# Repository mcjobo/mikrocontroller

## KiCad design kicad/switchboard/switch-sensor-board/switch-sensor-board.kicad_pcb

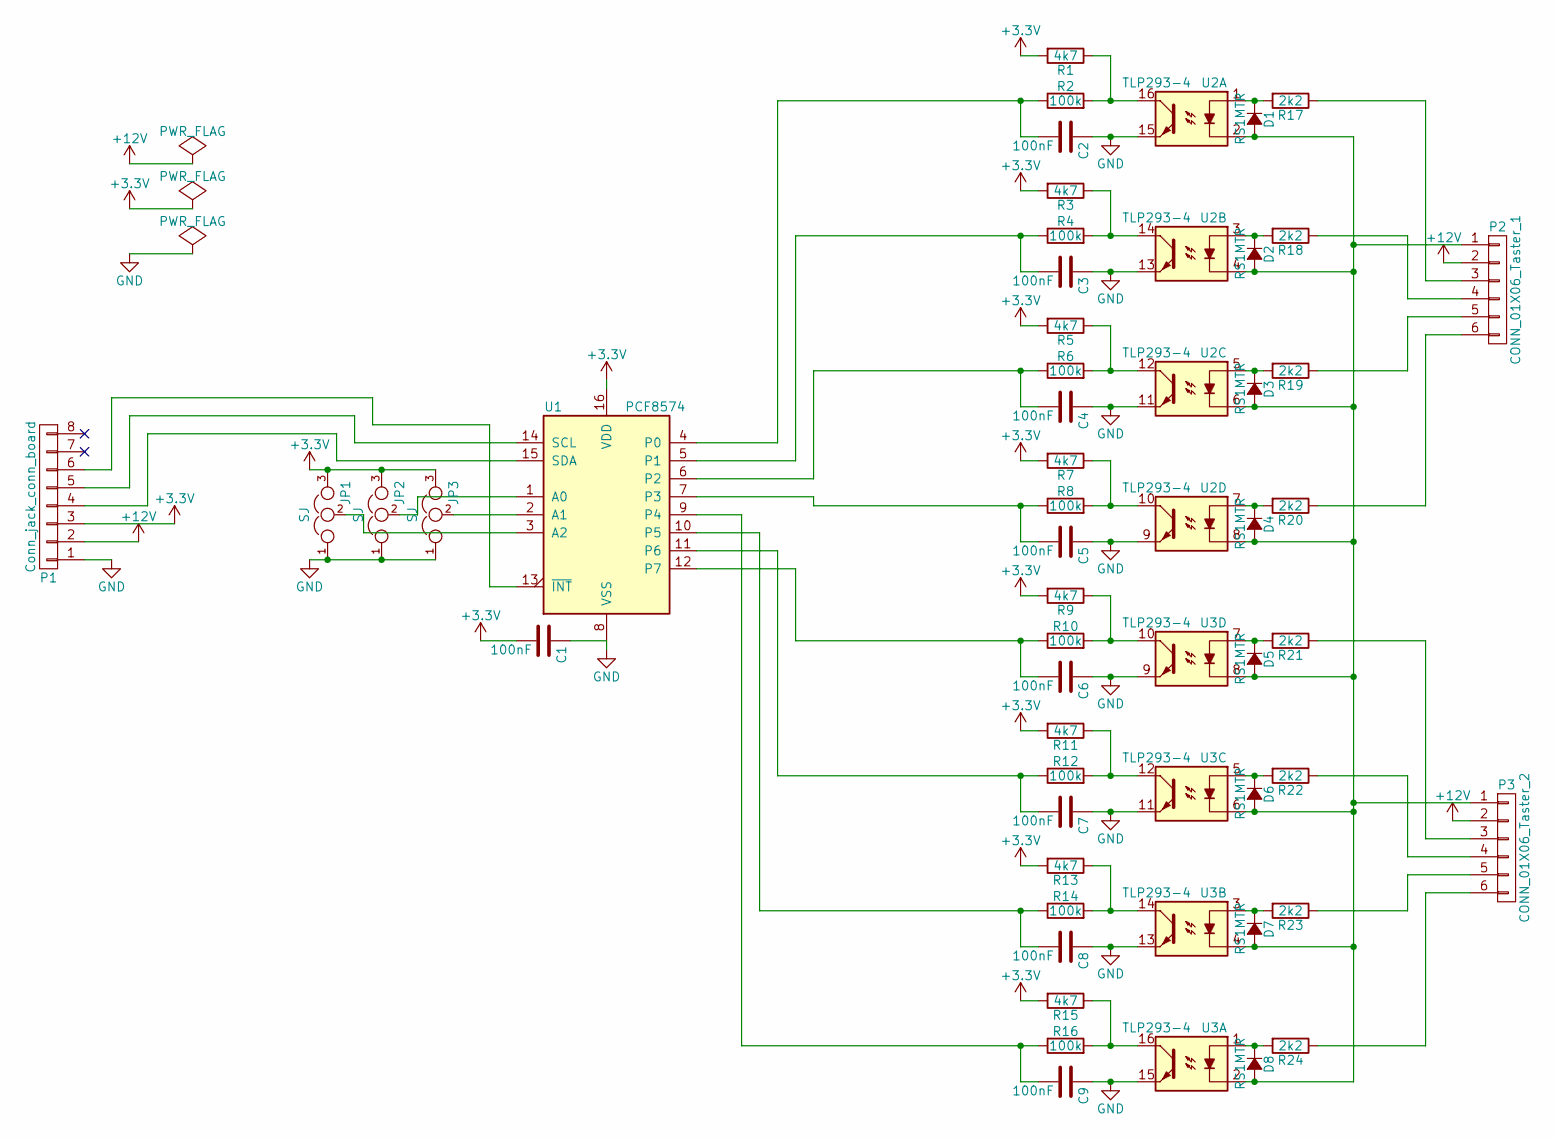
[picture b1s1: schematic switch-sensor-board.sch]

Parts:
C1, C2, C3, C4, C5, C6, C7, C8, C9: 100nF; C_1206_HandSoldering; Digi-Key 1276-2854-1-ND
D1, D2, D3, D4, D5, D6, D7, D8: RS1MTR; SMA_Handsoldering; Digi-Key 1655-1501-1-ND
JP1, JP2, JP3: SJ; solder-jumper-3er
P1: Conn_jack_conn_board; 4x2pin_50mil_header; Digi-Key S9007E-04-ND
P2: CONN_01X06_Taster_1; bornier6; Digi-Key ED2229-ND
P3: CONN_01X06_Taster_2; bornier6; Digi-Key ED2229-ND
R1, R3, R5, R7, R9, R11, R13, R15: 4k7; R_1206_HandSoldering; Digi-Key RHM4.7YCT-ND
R2, R4, R6, R8, R10, R12, R14, R16: 100k; R_1206_HandSoldering; Digi-Key RHM100KYCT-ND
R17, R18, R19, R20, R21, R22, R23, R24: 2k2; R_1206_HandSoldering; Digi-Key RHM2.2KYCT-ND
U1: PCF8574; SO-16-W; Digi-Key 568-1076-5-ND
U2, U3: TLP293-4; SO-16-N; Digi-Key TLP293-4(LGBE-ND

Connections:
+3V3: C1.2, JP1.3, JP2.3, JP3.3, P1.3, R1.2, R3.2, R5.2, R7.2, R9.2, R11.2, R13.2, R15.2, U1.16 (VDD)
+12V: P1.2, P2.2, P3.2
GND: C1.1, C2.1, C3.1, C4.1, C5.1, C6.1, C7.1, C8.1, C9.1, JP1.1, JP2.1, JP3.1, P1.1, U1.8 (VSS), U2.9, U2.11, U2.13, U2.15, U3.9, U3.11, U3.13, U3.15
unnamed: C2.2, R2.1, U1.4 (P0)
unnamed: C3.2, R4.1, U1.5 (P1)
unnamed: C4.2, R6.1, U1.6 (P2)
unnamed: C5.2, R8.1, U1.7 (P3)
unnamed: C6.2, R10.1, U1.12 (P7)
unnamed: C7.2, R12.1, U1.11 (P6)
unnamed: C8.2, R14.1, U1.10 (P5)
unnamed: C9.2, R16.1, U1.9 (P4)
unnamed: D1.1 (K), R17.2, U2.1
unnamed: D1.2 (A), D2.2 (A), D3.2 (A), D4.2 (A), D5.2 (A), D6.2 (A), D7.2 (A), D8.2 (A), P2.1, P3.1, U2.2, U2.4, U2.6, U2.8, U3.2, U3.4, U3.6, U3.8
unnamed: D2.1 (K), R18.2, U2.3
unnamed: D3.1 (K), R19.2, U2.5
unnamed: D4.1 (K), R20.2, U2.7
unnamed: D5.1 (K), R21.2, U3.7
unnamed: D6.1 (K), R22.2, U3.5
unnamed: D7.1 (K), R23.2, U3.3
unnamed: D8.1 (K), R24.2, U3.1
unnamed: JP1.2, U1.3 (A2)
unnamed: JP2.2, U1.1 (A0)
unnamed: JP3.2, U1.2 (A1)
unnamed: P1.4, U1.15 (SDA)
unnamed: P1.5, U1.14 (SCL)
unnamed: P1.6, U1.13 (~INT~)
unnamed: P2.3, R17.1
unnamed: P2.4, R18.1
unnamed: P2.5, R19.1
unnamed: P2.6, R20.1
unnamed: P3.3, R21.1
unnamed: P3.4, R22.1
unnamed: P3.5, R23.1
unnamed: P3.6, R24.1
unnamed: R1.1, R2.2, U2.16
unnamed: R3.1, R4.2, U2.14
unnamed: R5.1, R6.2, U2.12
unnamed: R7.1, R8.2, U2.10
unnamed: R9.1, R10.2, U3.10
unnamed: R11.1, R12.2, U3.12
unnamed: R13.1, R14.2, U3.14
unnamed: R15.1, R16.2, U3.16

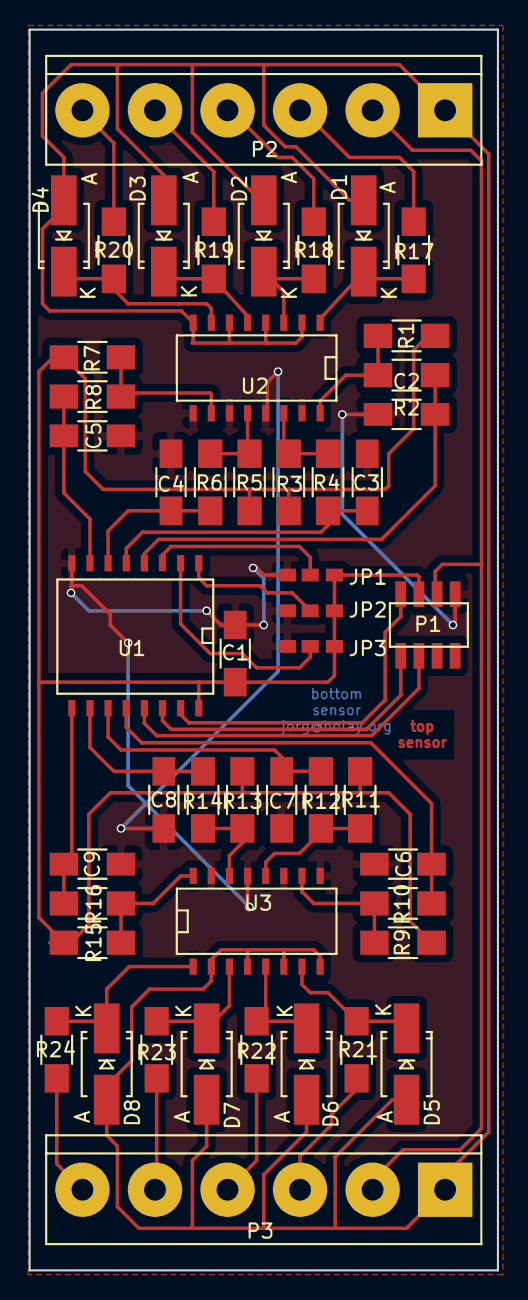
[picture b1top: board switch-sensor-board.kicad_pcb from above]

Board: 2 copper layers, 32.8 x 86.9 mm, 50 parts (0 on the bottom side), 42 nets.

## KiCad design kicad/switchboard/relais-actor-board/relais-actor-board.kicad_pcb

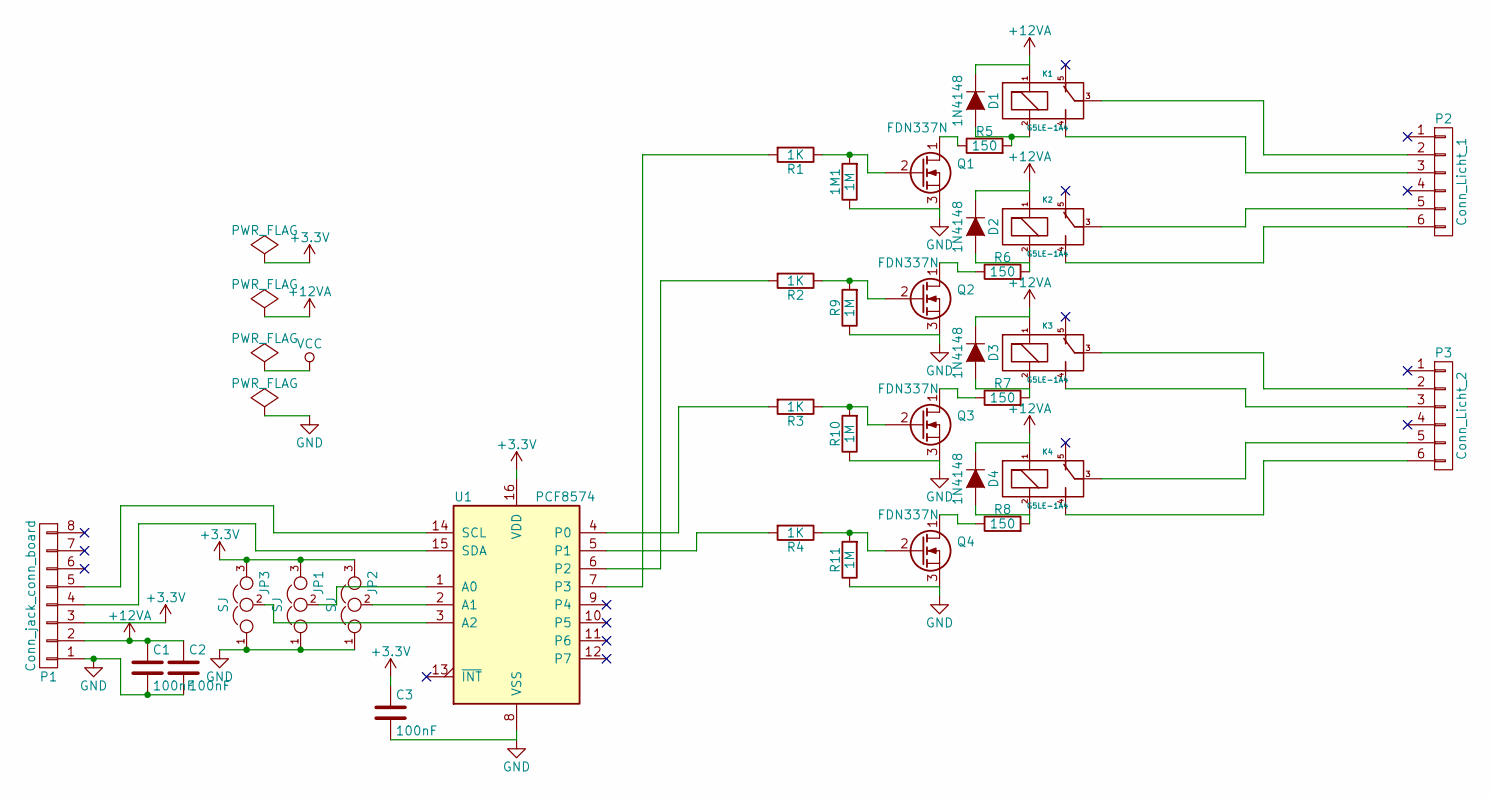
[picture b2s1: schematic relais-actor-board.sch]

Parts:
1M1: 1M; R_1206_HandSoldering; Digi-Key 311-1.0MERCT-ND
C1, C2, C3: 100nF; C_1206_HandSoldering; Digi-Key 1276-2854-1-ND
D1, D2, D3, D4: 1N4148; SOD-123; Digi-Key 1N4148W-FDICT-ND
JP1, JP2, JP3: SJ; solder-jumper-3er
K1, K2, K3, K4: G5LE-1A4; Relais-12V-Schlieser; Digi-Key PB876-ND
P1: Conn_jack_conn_board; 4x2pin_50mil_header; Digi-Key S9007E-04-ND
P2: Conn_Licht_1; bornier6; Digi-Key ED2229-ND
P3: Conn_Licht_2; bornier6; Digi-Key ED2229-ND
Q1, Q2, Q3, Q4: FDN337N; SOT-23_Handsoldering-FDN-337N; Digi-Key FDN337NTR-ND
R1, R2, R3, R4: 1K; R_1206_HandSoldering; Digi-Key 311-1.0KERCT-ND
R5, R6, R7, R8: 150; R_1206_HandSoldering; Digi-Key RHM150YCT-ND
R9, R10, R11: 1M; R_1206_HandSoldering; Digi-Key 311-1.0MERCT-ND
U1: PCF8574; SO-16-W; Digi-Key 568-1076-5-ND

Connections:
+3V3: C3.1, JP1.3, JP2.3, JP3.3, P1.3, U1.16 (VDD)
+12VA: C1.1, C2.1, D1.1 (K), D2.1 (K), D3.1 (K), D4.1 (K), K1.1, K2.1, K3.1, K4.1, P1.2
GND: 1M1.1, C1.2, C2.2, C3.2, JP1.1, JP2.1, JP3.1, P1.1, Q1.3 (S), Q2.3 (S), Q3.3 (S), Q4.3 (S), R9.1, R10.1, R11.1, U1.8 (VSS)
unnamed: 1M1.2, Q1.2 (G), R1.1
unnamed: D1.2 (A), K1.2, R5.2
unnamed: D2.2 (A), K2.2, R6.2
unnamed: D3.2 (A), K3.2, R7.2
unnamed: D4.2 (A), K4.2, R8.2
unnamed: JP1.2, U1.1 (A0)
unnamed: JP2.2, U1.2 (A1)
unnamed: JP3.2, U1.3 (A2)
unnamed: K1.3, P2.2
unnamed: K1.4, P2.3
unnamed: K2.3, P2.5
unnamed: K2.4, P2.6
unnamed: K3.3, P3.2
unnamed: K3.4, P3.3
unnamed: K4.3, P3.5
unnamed: K4.4, P3.6
unnamed: P1.4, U1.15 (SDA)
unnamed: P1.5, U1.14 (SCL)
unnamed: Q1.1 (D), R5.1
unnamed: Q2.1 (D), R6.1
unnamed: Q2.2 (G), R2.1, R9.2
unnamed: Q3.1 (D), R7.1
unnamed: Q3.2 (G), R3.1, R10.2
unnamed: Q4.1 (D), R8.1
unnamed: Q4.2 (G), R4.1, R11.2
unnamed: R1.2, U1.7 (P3)
unnamed: R2.2, U1.6 (P2)
unnamed: R3.2, U1.4 (P0)
unnamed: R4.2, U1.5 (P1)

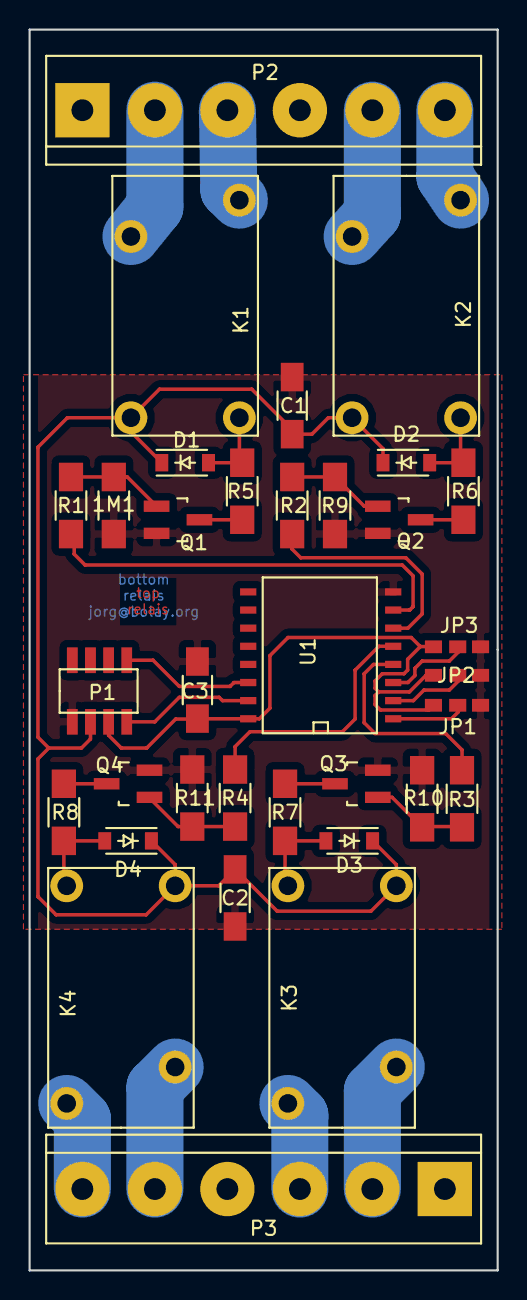
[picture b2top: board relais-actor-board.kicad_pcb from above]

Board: 2 copper layers, 32.8 x 86.9 mm, 34 parts (0 on the bottom side), 32 nets.

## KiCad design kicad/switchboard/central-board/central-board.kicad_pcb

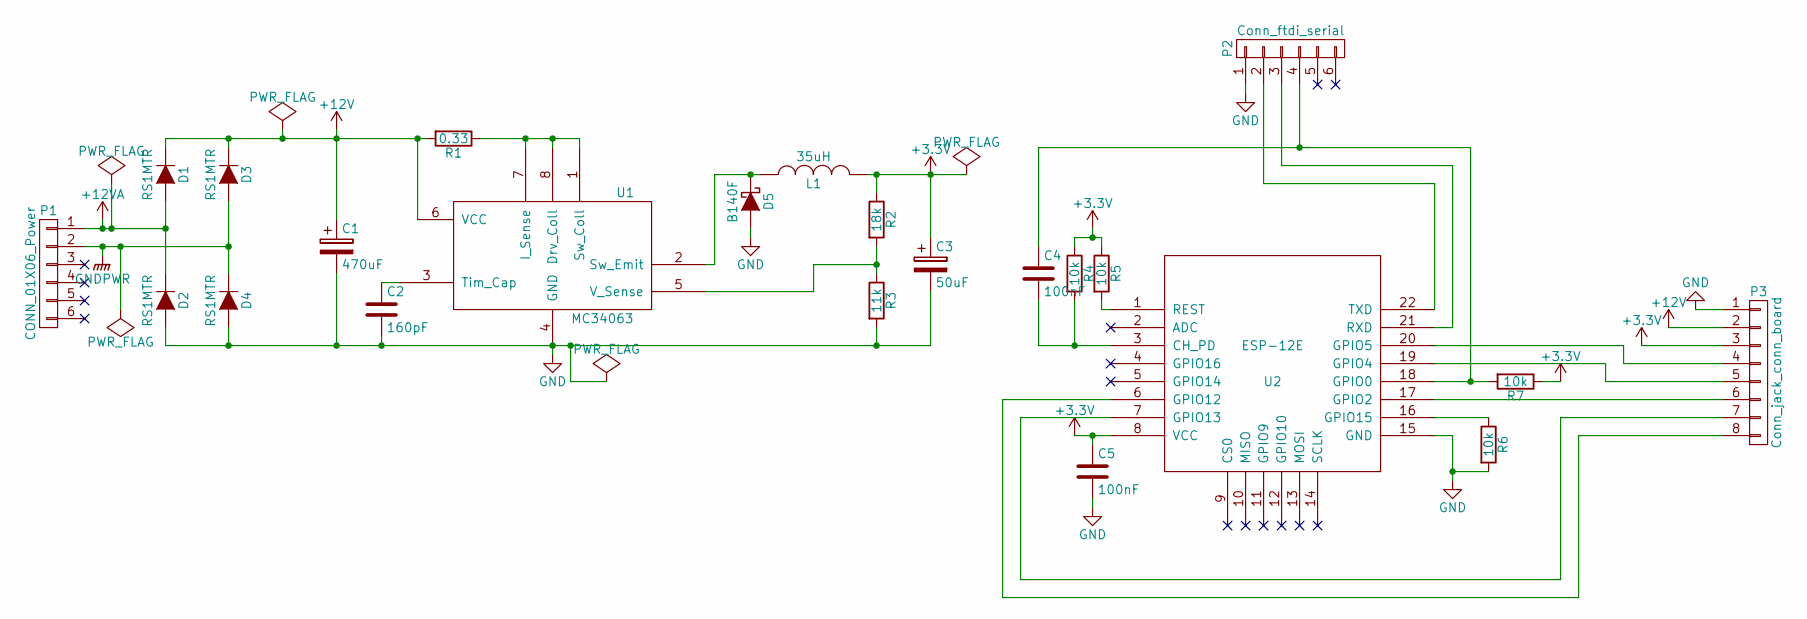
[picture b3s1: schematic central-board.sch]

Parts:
C1: 470uF; c_elec_10x10.5
C2: 160pF; C_1206_HandSoldering; Digi-Key 1276-2811-1-ND
C3: 50uF; c_elec_6.3x7.7; Digi-Key vorhanden
C4, C5: 100nF; C_1206_HandSoldering; Digi-Key 1276-2854-1-ND
D1, D2, D3, D4: RS1MTR; SMA_Handsoldering; Digi-Key 1655-1501-1-ND
D5: B140F; SMA_Handsoldering; Digi-Key vorhanden
L1: 35uH; SRN_1060_Power_Inductors; Digi-Key SRN1060-470MCT-ND
P1: CONN_01X06_Power; bornier6; Digi-Key ED2229-ND
P2: Conn_ftdi_serial; 6x1pin_50mil_header; Digi-Key S9005E-06-ND
P3: Conn_jack_conn_board; 4x2pin_50mil_header; Digi-Key S9007E-04-ND
R1: 0.33; R_1206_HandSoldering; Digi-Key A103274CT-ND
R2: 18k; R_1206_HandSoldering; Digi-Key 311-18KERCT-ND
R3: 11k; R_1206_HandSoldering; Digi-Key RC1206JR-0711KL
R4, R5, R6, R7: 10k; R_1206_HandSoldering; Digi-Key RHM10KZCT-ND
U1: MC34063; SOIC-8-N; Digi-Key 497-7852-1-ND
U2: ESP-12E; Digi-Key vorhanden

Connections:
+3V3: C3.1, C5.1, L1.2, P3.3, R2.1, R4.1, R5.1, R7.1, U2.8 (VCC)
+12V: C1.1, D1.1 (K), D3.1 (K), P3.2, R1.2, U1.6 (VCC)
+12VA: D1.2 (A), D2.1 (K), P1.1
GND: C1.2, C2.2, C3.2, C5.2, D2.2 (A), D4.2 (A), D5.2 (A), P2.1, P3.1, R3.2, R6.2, U1.4 (GND), U2.15 (GND)
GNDPWR: D3.2 (A), D4.1 (K), P1.2
unnamed: C2.1, U1.3 (Tim_Cap)
unnamed: C4.1, P2.4, R7.2, U2.18 (GPIO0)
unnamed: C4.2, R4.2, U2.3 (CH_PD)
unnamed: D5.1 (K), L1.1, U1.2 (Sw_Emit)
unnamed: P2.2, U2.22 (TXD)
unnamed: P2.3, U2.21 (RXD)
unnamed: P3.4, U2.20 (GPIO5)
unnamed: P3.5, U2.19 (GPIO4)
unnamed: P3.6, U2.17 (GPIO2)
unnamed: P3.7, U2.7 (GPIO13)
unnamed: P3.8, U2.6 (GPIO12)
unnamed: R1.1, U1.1 (Sw_Coll), U1.7 (I_Sense), U1.8 (Drv_Coll)
unnamed: R2.2, R3.1, U1.5 (V_Sense)
unnamed: R5.2, U2.1 (REST)
unnamed: R6.1, U2.16 (GPIO15)

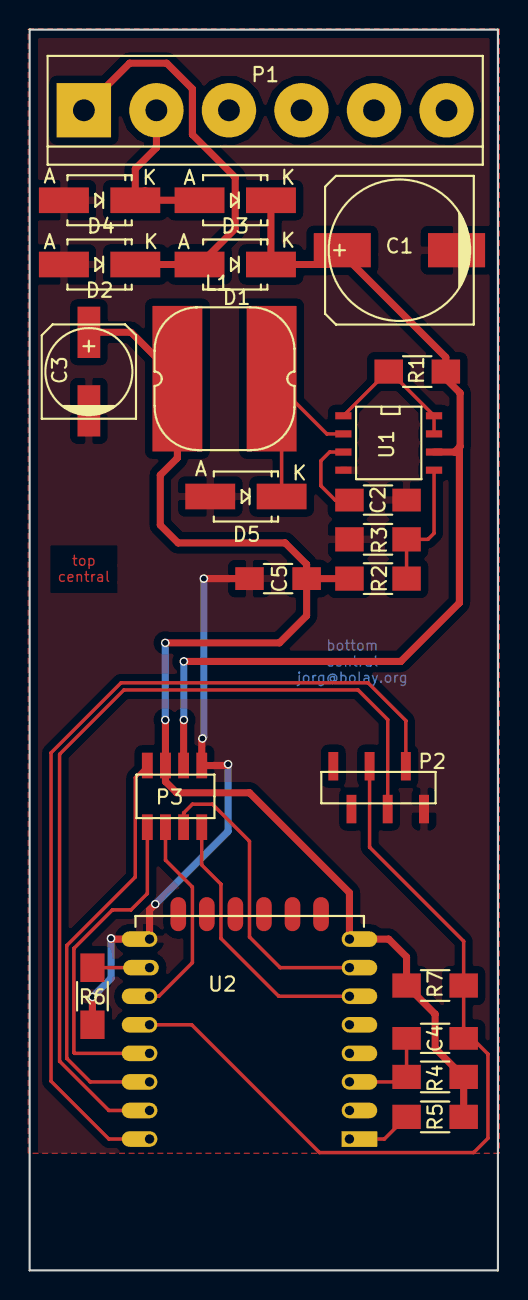
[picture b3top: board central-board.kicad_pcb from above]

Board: 2 copper layers, 32.8 x 86.9 mm, 23 parts (0 on the bottom side), 20 nets.

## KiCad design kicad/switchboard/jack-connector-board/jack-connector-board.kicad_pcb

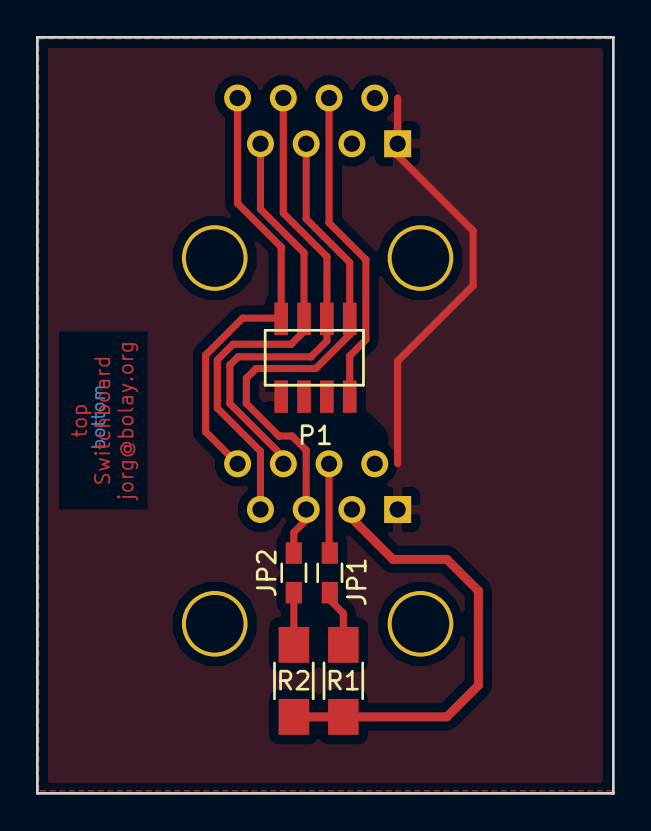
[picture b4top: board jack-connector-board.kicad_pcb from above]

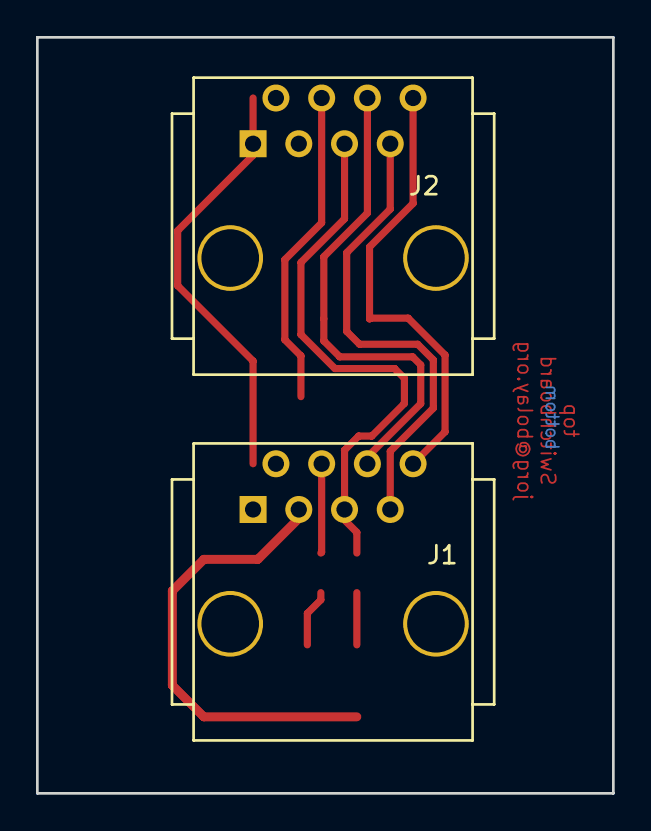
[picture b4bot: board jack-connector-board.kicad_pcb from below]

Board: 2 copper layers, 32.0 x 42.0 mm, 7 parts (2 on the bottom side), 10 nets.

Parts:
J1, J2: ConnBus; RJ45_vertical_8
JP1, JP2: Jumper_NC_Small; R_0603_HandSoldering
P1: ConnMainboard; 4x2pin_50mil_header
R1, R2: 4,7k; R_1206_HandSoldering

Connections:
+3V3: J1.3, J2.3, P1.3, R1.1, R2.1
+12V: J1.2, J2.2, P1.2
GND: J1.1, J2.1, P1.1
unnamed: J1.4, J2.4, JP1.1, P1.4
unnamed: J1.5, J2.5, JP2.1, P1.5
unnamed: J1.6, J2.6, P1.6
unnamed: J1.7, J2.7, P1.7
unnamed: J1.8, J2.8, P1.8
unnamed: JP1.2, R1.2
unnamed: JP2.2, R2.2

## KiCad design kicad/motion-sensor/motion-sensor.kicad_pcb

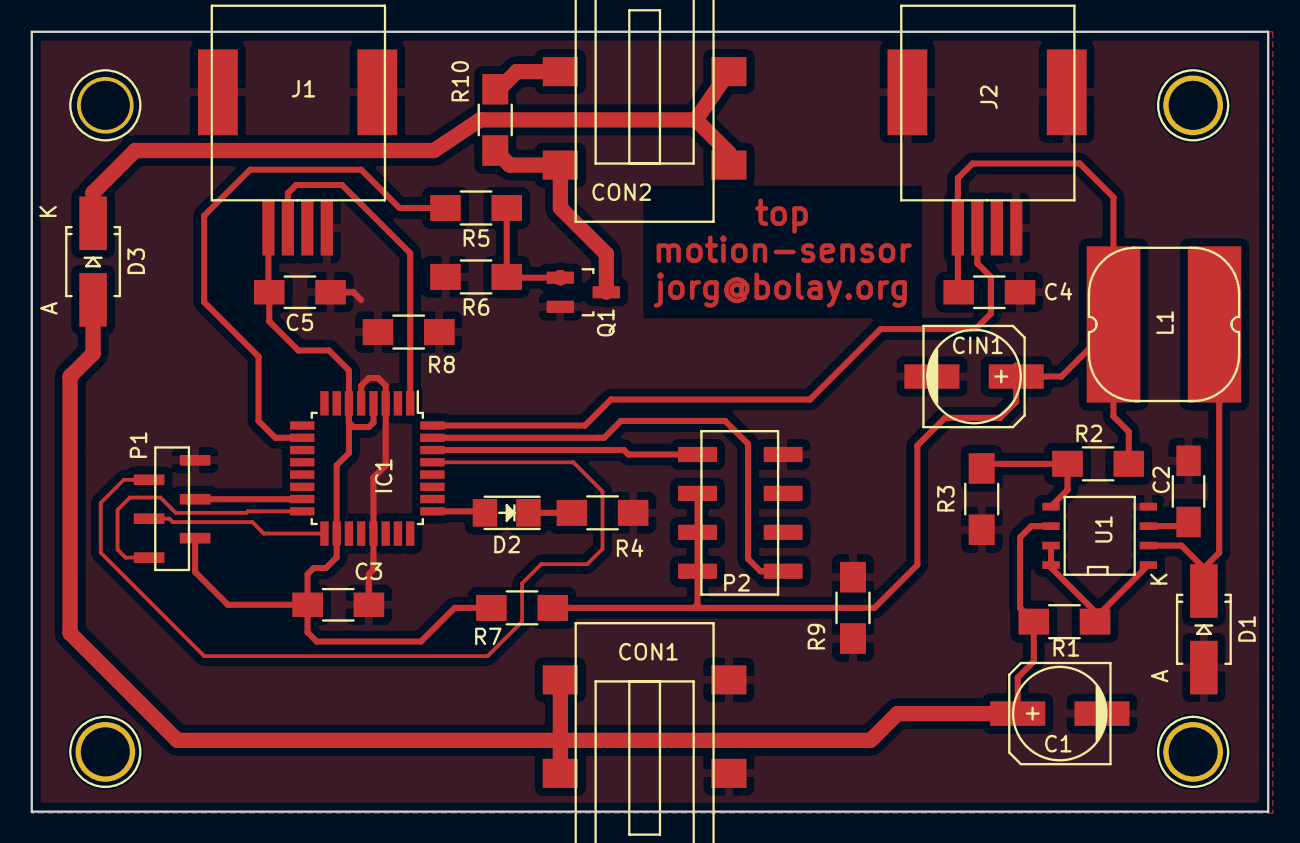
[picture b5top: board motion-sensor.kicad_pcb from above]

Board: 2 copper layers, 80.7 x 50.9 mm, 29 parts (0 on the bottom side), 22 nets.

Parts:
C1: 100uF; c_elec_6.3x7.7
C2: 160pF; C_1206_HandSoldering
C3, C4, C5: 100nF; C_1206_HandSoldering
CIN1: 50uF; c_elec_6.3x7.7
CON1, CON2: LUM 1613-14; barrel_jack_ds_1613_14
D1, D3: B140F; SMA_Handsoldering
D2: LED; LED_1206
IC1: ATMEGA328P-A AU 1537; TQFP-32_7x7mm_Pitch0.8mm
J1, J2: RJ10_4p4c; RJ10_SMD_4p4c
L1: 35uH; SRN_1060_Power_Inductors
P1: ISP; 6x1pin_50mil_header
P2: ESP8266; 8pin_Header_SMD
Q1: FDN337N; SOT-23_Handsoldering
R1: 0.33; R_1206_HandSoldering
R2: 18k; R_1206_HandSoldering
R3: 11k; R_1206_HandSoldering
R4: 560; R_1206_HandSoldering
R5: 1K; R_1206_HandSoldering
R6: 1M; R_1206_HandSoldering
R7, R8, R9, R10: 0; R_1206_HandSoldering
U1: MC34063; SOIC-8-N

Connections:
+3V3: C3.1, C4.1, C5.1, CIN1.1, IC1.4, IC1.6, IC1.18, J1.1, J2.1, L1.2, P1.2, P2.2, P2.4, P2.6, R2.1, R7.1, R7.2
+12V: C1.1, CON1.1, D3.2, R1.2, U1.6
GND: C1.2, C2.2, C3.2, C4.2, C5.2, CIN1.2, CON1.2, CON1.3, D1.2, IC1.3, IC1.5, IC1.21, J1.4, J1.5, J1.6, J2.4, J2.5, J2.6, P1.6, P2.7, Q1.3, R3.1, R4.2, R6.2, R8.1, R8.2, R9.1, R9.2, U1.4
LED_PIN: D2.2, IC1.25
MISO: IC1.16, P1.1
MOSI: IC1.15, P1.4
Motion_Sensor_Pin_1: IC1.1, J1.2
Motion_Sensor_Pin_2: IC1.32, J2.2
unnamed: C2.1, U1.3
unnamed: CON2.1, D3.1
unnamed: CON2.2, Q1.1, R10.1
unnamed: CON2.3, R10.2
unnamed: D1.1, L1.1, U1.2
unnamed: D2.1, R4.1
unnamed: Q1.2, R5.1, R6.1
unnamed: R1.1, U1.1, U1.7, U1.8
unnamed: R2.2, R3.2, U1.5
PWM_Pin: IC1.10, R5.2
RESET: IC1.29, P1.5
RXD: IC1.30, P2.8
SCK: IC1.17, P1.3
TXD: IC1.31, P2.1

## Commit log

2013-09-02 commited test
2013-09-07 added rfm12 testboard project
2013-09-16 removed the packet type or address field because it needs to be in the higher layer
2013-09-16 fixed something don't realy know what's going on
2013-09-16 added solution file
2013-09-23 added protocol implementation
2013-09-27 added statemachine files
2013-09-27 added timer functions
2013-09-27 changed symbols from atmega8 to atmega 88A
2013-10-06 ÜbungsProjekt TestBoard
2013-10-12 added rfm12 module and fixed project setup to create library
2013-10-12 fixing problems with ack creation of protocol
2013-10-12 added procyon avrlib to the project
2013-10-12 build rfm12 as library and have the protocol implementation also as library
2013-10-16 fixed the rfm12 library to work again as a static library
2013-10-17 added network components
2013-10-19 added openmcp project
2013-10-29 reimplemented the protocol impl to have a proper state maschine and clean code
2013-10-29 moved new protocol in place
2013-10-31 reducing size of project
2013-10-31 first try in connecting io-board to openhab
2013-11-03 added basic sending capabilities to openhab port impl
2013-12-26 reimplemented statemachine to rfm12 library to working state
2013-12-31 added additional lib to project
2013-12-31 new project to build a driver for led strips with PWM LDR and motion sensor
2014-01-02 uart project from peter leury
2014-02-01 breadboard type of prototypeworking + added a2d lib
2015-11-03 initial commit ir-receiver + sender
2015-11-08 ir_receive project
2015-11-08 ir_send vorläufig fertig
2015-11-08 common files
2015-12-11 projekt weinachtsbild beleuchtung working
2015-12-11 changed uart lib to use the smarthomatic one and use a extra lib for leds
2015-12-11 just a simple project to test the uart connection
2015-12-11 sublime project files
2015-12-11 changed to other uart lib
2015-12-11 don't know where i am just saving
2015-12-11 added eagle files to repo
2015-12-11 added kicad files to the repo
2015-12-12 fixed 12V on motion sensor and other components
2015-12-12 fiddleling with MAC adresses
2015-12-14 added component lines + enclosure infos
2016-01-02 added custom footprints and finished schematic
2016-01-02 changed string parsing to hex numbers added ir protocols for micha
2016-01-09 changed ir_receiver output to hex
2016-02-15 motion sensor project in kicad
2016-11-05 motion sensor Projekt für Küche und unter dem Bett
2016-11-05 initiales Projekt Switchboard
2016-11-05 motion sensor projekt
2016-11-05 bibliotheks aenderungen
2016-11-05 programm für das Bewegungsmelder Projekt
2016-11-06 der switchboard schaltplan wurde angefangen
2016-12-20 added switchboard project
2016-12-21 changed files of motion sensor project and library
2016-12-25 zusätzliche modi beim motion sensor: 0: off 1: on 2: bewegung
2016-12-26 fading funktioniert beschreibungsdatei für mqtt topics hinzugefügt mqtt topics im ino file etwas auseinandergezogen
2016-12-26 rduino projekt
